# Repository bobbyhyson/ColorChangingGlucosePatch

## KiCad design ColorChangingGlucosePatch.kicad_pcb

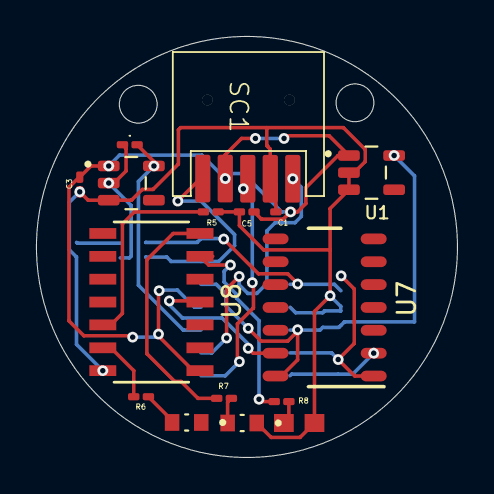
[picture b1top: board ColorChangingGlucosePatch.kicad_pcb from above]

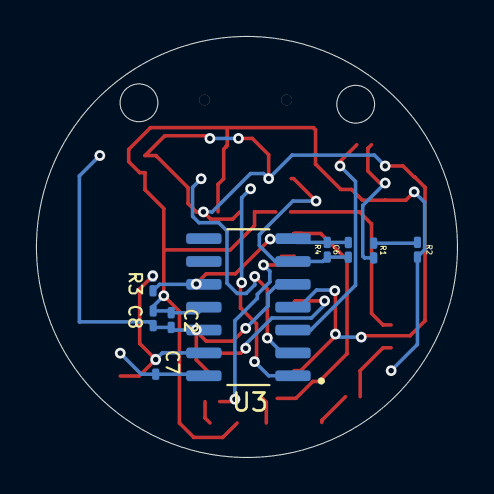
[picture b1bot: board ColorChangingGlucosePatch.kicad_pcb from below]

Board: 2 copper layers, 23.4 x 23.4 mm, 25 parts (9 on the bottom side), 21 nets.

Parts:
C1, C3: 1uF; C_0201_0603Metric_Pad0.64x0.40mm_HandSolder
C2, C4: 2.2uF; C_0201_0603Metric_Pad0.64x0.40mm_HandSolder
C5, C8: 100nF; C_0201_0603Metric_Pad0.64x0.40mm_HandSolder
C6: 10nF; C_0201_0603Metric_Pad0.64x0.40mm_HandSolder
C7: 100uF; C_0201_0603Metric_Pad0.64x0.40mm_HandSolder
D1: YLLW; LEDC1608X35N
D2: RED; 0603
D3: GRN; LEDC1608X35N
R1: 130k; C_0201_0603Metric_Pad0.64x0.40mm_HandSolder
R2: 180k; C_0201_0603Metric_Pad0.64x0.40mm_HandSolder
R3, R4: 100k; C_0201_0603Metric_Pad0.64x0.40mm_HandSolder
R5: 10k; C_0201_0603Metric_Pad0.64x0.40mm_HandSolder
R6, R7, R8: 180; C_0201_0603Metric_Pad0.64x0.40mm_HandSolder
SC1: Strip-Connector
U1, U2: TPS76925DBVR; SOT95P280X145-5N
U3: LMC6484; SOIC127P600X175-14N
U7: CD4066BM96; D0014A_N
U8: ATTINY204-SSFR; SOIC14_SL_MCH

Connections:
+2.1V: C4.1, U2.5 (OUT), U3.3 (+)
+2.5V: C2.1, C8.1, U1.5 (OUT), U3.5 (+), U3.12 (+), U7.14 (VDD)
+5V: C1.1, C3.1, C5.1, SC1.4, U1.1 (IN), U2.1 (IN), U3.4 (V+), U8.1 (VDD)
GND: C1.2, C2.2, C3.2, C5.2, C8.2, D1.C, D2.1, D3.C, R2.2, R5.2, SC1.2, U1.2 (GND), U1.3 (EN), U2.3 (EN), U3.11 (V-), U8.14 (GND)
unnamed: D1.A, R7.2
unnamed: D2.2, R8.2
unnamed: D3.A, R6.2
unnamed: R1.2, R2.1
unnamed: SC1.3, U3.1
unnamed: R5.1, U8.12 (PA2)
unnamed: SC1.1, U3.2 (-)
unnamed: C6.1, R4.1, SC1.5, U3.6 (-)
unnamed: C4.2, R1.1, U2.2 (GND)
unnamed: C6.2, R3.1, R4.2, U3.7, U3.10 (+)
unnamed: U3.8, U3.9 (-)
unnamed: C7.1, R3.2, U3.13 (-), U7.1 (SIG_A_IN_OUT)
unnamed: U7.13 (CONTROL_A), U8.4 (PA6)
unnamed: C7.2, U3.14, U7.2 (SIG_A_OUT_IN)
unnamed: R6.1, U8.13 (PA3/EXTCLK)
unnamed: R7.1, U8.7 (PB2)
unnamed: R8.1, U8.6 (PB3)

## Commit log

2025-11-11 work please
2025-11-11 please work
2025-11-14 more stuff
2025-11-14 telling josh he is lame
2025-11-18 holy shit its working
2025-11-19 late to gym oh no
2025-11-19 goddamnit
2025-11-19 oh no
2025-11-19 final version but its not because im probably gonna work on it tomorrow.
2025-11-19 fuck this
2025-11-19 sleepy
2025-11-20 final revision but not really
